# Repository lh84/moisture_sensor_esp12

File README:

# Bodenfeuchte Sensor mit einem ESP12 (Wifi/Wlan)

Dieser Sensor ist noch in Bearbeitung. Es soll dazu dienen, die Bodenfeuchte von Pflanzen zu messen und per WLan an einen Server zur Datenauswertung zu senden. Für das Sender per Wlan wird ein ESP8266 Modul verwendet. Als Sensor kommt eine kapazitive Messmethode zum Einsatz. Das  Grundgerüst des Sensors basiert auf den [Gies-O-Mat von Fred Ram][1].

## Stromquelle

ALs Stromquelle soll ein 18650 AKku dienen, da dieser über hohe Kapazitäten verfügen kann. So kann eine lange Lebensdauer pro Batterie gewährleistet werden. Es wird davon ausgegangen, dass der Sensor bei halbstündiger Messung bis zu 3 Monate arbeiten kann. (Dies muss noch bewiesen werden)

## bisherige Part-Liste

Part       Value          Device     Package  Library        Sheet

1RX-2TX                   PINHD-1X2  1X02     pinhead        1
13,3V-2GND                PINHD-1X2  1X02     pinhead        1
C1         1000µF         CP-SV-E/F  SV-E/F   cap-master     1
C2         10µF           C1206      1206     capsmd         1
C4         10µF           C1206      1206     capsmd         1
ESP                       ESP12      ESP12    esp8266modules 1
GND                       PINHD-1X1  1X01     pinhead        1
IC1        74HC14D        74HC14D    SO14     74xx-eu        1
IC2        HT7333         HT7333     SOT-89   holtek2        1
PAD1                      2,54/1,0   2,54/1,0 wirepad        1
PAD2                      2,54/1,0   2,54/1,0 wirepad        1
PROG       DTSM-6         DTSM-6     DTSM-6   switch-tact    1
R2         ca 100k        R-EU_R0603 R0603    rcl            1
R3         100            R-EU_R0603 R0603    rcl            1
RESET      DTSM-6         DTSM-6     DTSM-6   switch-tact    1
VIN                       PINHD-1X1  1X01     pinhead        1

## Contribute?

Du möchtest mithelfen, dass Design oder die Software zu verbessern? Dann schreib mir oder sende ein Request.

[1]: https://www.mikrocontroller.net/topic/335407

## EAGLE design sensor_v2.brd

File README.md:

REV 1.0

# Moisture Sensor with an ESP8266 12F (Wifi/Wlan)

This project is still work in progress!

This sensor is intended to measure the soil moisture of plants and to send them by WIFI to a server for data evaluation. An ESP8266 module is used for the sender to send data over the air. A capacitive measuring method is used as a sensor to get moisture values. The basic framework of the sensor is based on the [Gies-O-Mat von Fred Ram]<sup>[1]</sup>.

## power source

A 18650 battery is to be used as power source, as this can have high capacities. A long life per battery can be guaranteed. It is assumed that the sensor can operate for up to 3 months at half-hour measurement - This must still be proven!

## Board-Layout

Layout was made with Eagle 7.7<sup>[2]</sup>.

First try to model a case for the board in 3d

GPIO5 is now used to control Vin in smitt trigger to use less power when sensor is not measuring.

## Part-List

| Qty | Value           | Device      | Package     | Parts               | Description                              | Price per pc     | Order-Link                                                                                                                                             | 
|-----|-----------------|-------------|-------------|---------------------|------------------------------------------|------------|--------------------------------------------------------------------------------------------------------------------------------------------------| 
| 2   | PINHD-1X2       | 1X02        | 1RX-2TX     | 3,3V-2GND           | PIN HEADER                               | 0,28 € (0,71 € / 10pc) | https://www.reichelt.de/Buchsenleisten/MPE-115-1-010/3/index.html?ACTION=3&LA=2&ARTICLE=119955&GROUPID=7435&artnr=MPE+115-1-010&SEARCH=%252A     | 
| 1   | 100Ω             |  R-EU_R0603 | R0603       | R3                  | RESISTOR, European symbol                | 0,02 €   | https://www.reichelt.de/SMD-0603-von-0-bis-910-Ohm/RND-0603-1-100/3/index.html?ACTION=3&LA=5&ARTICLE=183013&GROUPID=7967&artnr=RND+0603+1+100    | 
| 1   | 1000µF          | CP-SV-E/F   | SV-E/F      | C1                  |  Big POLARIZED CAP                       | 0,32 €  | https://www.reichelt.de/Elkos-SMD-Low-ESR-105-C/VF-1000-6-3-P-F/3/index.html?ACTION=3&LA=5&ARTICLE=109181&GROUPID=4001&artnr=VF+1000%2F6%2C3+P-F | 
| 2   | 10µF            | C1206       | 1206        | C2, C4              | Small SMD Cap                            | 0,07 €   | https://www.reichelt.de/Vielschicht-SMD-G1206/X7R-G1206-10-16/3/index.html?ACTION=3&LA=5&ARTICLE=89740&GROUPID=8049&artnr=X7R-G1206+10%2F16      | 
| 1   | 500KΩ            | R-TRIMM3374 | R-TRIMM3374 | R1TRIM              | Trimm resistor til 500KΩ                 | 0,67 €  | https://www.reichelt.de/Miniaturtrimmer/23B-500K/3/index.html?ACTION=3&GROUPID=3131&ARTICLE=146090&OFFSET=16&                                    | 
| 1   | 74HC14D 74HC14D | SO14        | IC1         | Hex schmitt trigger | INVERTER                                 | 0,18 €  | https://www.reichelt.de/ICs-74HC-SMD/SMD-HC-14/3/index.html?ACTION=3&GROUPID=2931&ARTICLE=18640&SEARCH=74HC14&OFFSET=16&                         | 
| 2   | DTSM-6  DTSM-6  | DTSM-6      | PROG, RESET |                     | Push button                              | 0,24 €  | https://www.reichelt.de/Kurzhubtaster/TASTER-9314/3/index.html?ACTION=3&GROUPID=7587&ARTICLE=44510&OFFSET=500&                                   | 
| 1   | ESP12           | ESP12       | ESP12       | ESP                 | ESP8266 Wifi module 12                   | 2,54 €  | https://www.aliexpress.com/item/1-pcs-x-ESP-12F-ESP8266-ESP-12F-Remote-Serial-Port-WIFI-Transceiver-Wireless-Module-UNO/32581210212.html         | 
| 1   | HT7333          | HT7333      | SOT-89      | IC2                 | Step Down Module (Ultra low current 4µA) | 0,12 € (1,18€ / 10pc) | https://www.aliexpress.com/item/10PCS-HT7333-A-SOT89-HT7333-1-SOT-89-HT7333A-1-7333-1-SMD-7333A-1-new/32531141419.html                           | 
| 2   | LSP11           | LSP11       | LSP11       | LSP1, LSP2          | SOLDER PAD                               | no costs   |                                                                                                                                                  | 
| 1   | Platine         | EPCU        |             |                     | Size 200X100, one side copper            | 0,58 € (1,75 €) | https://www.reichelt.de/Platinenzuschnitte/EPCU-200X100/3/index.html?ACTION=3&LA=2&ARTICLE=7408&GROUPID=7783&artnr=EPCU+200X100&SEARCH=%252A     |
| 1 | Accu 18650       |         |             |                     | e.g. LG ICR18650S3 - 2200mAh, 3,6 - 3,7V Lithium Ionen Akku | 3,95 € | https://www.akkuteile.de/lg-icr18650s3-2200mah/a-100629 |
| 1 |  18650 Holder     |         |             |                     | | 0,44 € | https://de.aliexpress.com/item/Hot-With-Wire-Lead-Plastic-18650-Battery-3-7V-Clip-Holder-Storage-Box-Case-Cheap-Sale/32458234409.html |
||
|**Sum**||||||**10,00€ + shipping + work**||

Reichelt Order List: https://www.reichelt.de/my/1310317

see also file https://github.com/lh84/moisture_sensor_esp12/blob/master/bom.txt

## Software

As software you can use the source code von Zentris<sup>[3]</sup>. Version 2.2 works pretty good with some small changes.

## Testing

First test at 20/01/17 was pretty good with this new designed board.

## Prototypes

I made a first prototype of the new design with etching at home. Looks und works pretty good for the first test.

## First tests with prototype

You can see the live data from my first sensor prototype monitored in thingspeak:
https://thingspeak.com/channels/210863/charts/1?width=1000&height=600&bgcolor=%23ffffff&color=%23d62020&results=240&type=line&update=15&timescale=240

## Contribute?

You have an idea how this sensor can be designed better? Then write me or send a request.

## TODO
- [ ] Model case for board (fusion 360)
- [ ] Add battery monitoring with voltage devider (http://www.esp8266-projects.com/2015/03/internal-adc-esp8266.html)

## Done
- [x] build first prototype
- [x] check hardware (first prototype)
- [x] check runtime with 18650 battry - see comments in https://github.com/lh84/moisture_sensor_esp12/issues/3
- [x] test hardware in outdoor environment

[1]: https://www.mikrocontroller.net/topic/335407
[2]: https://cadsoft.io/de/
[3]: https://github.com/Zentris/erdfeuchtemessung

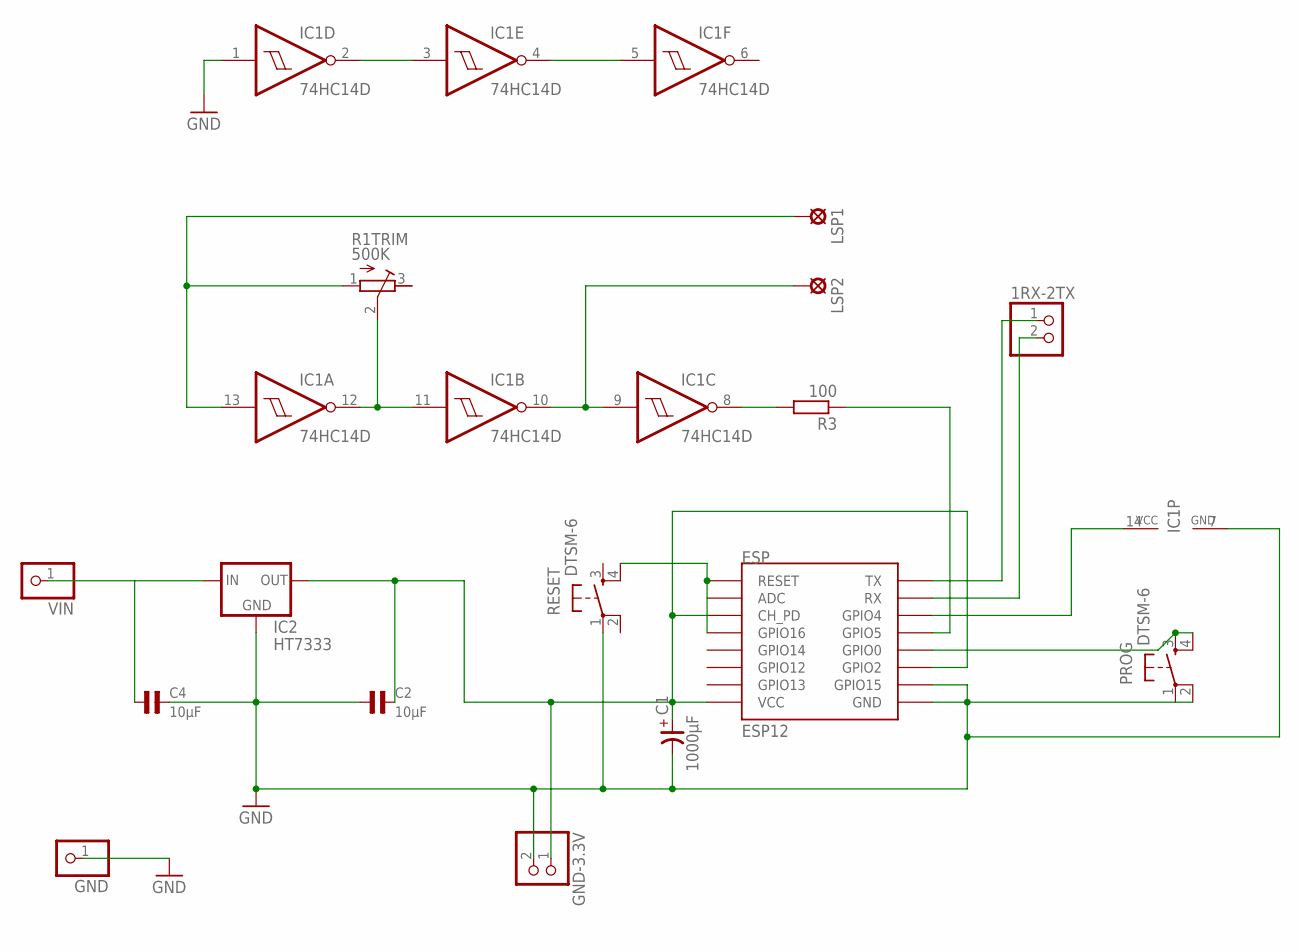
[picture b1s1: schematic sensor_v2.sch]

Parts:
1RX-2TX: PINHD-1X2; 1X02
C1: 1000µF; SV-E/F
C2, C4: 10µF; 1206
ESP: ESP12
GND: PINHD-1X1; 1X01
GND-3.3V: PINHD-1X2; 1X02
IC1: 74HC14D; SO14
IC2: HT7333; SOT-89
LSP1, LSP2: LSP11
PROG: DTSM-6
R1TRIM: 500K; RTRIM3374
R3: 100; R0603
RESET: DTSM-6
VIN: PINHD-1X1; 1X01

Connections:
3.3V: C1.+, C2.2, ESP.CH_PD, ESP.GPIO2, ESP.VCC, GND-3.3V.1, IC2.1 (OUT)
BIS6VVCC: C4.1, IC2.3 (IN), IC2.4 (IN), VIN.1
GND: C1.-, C2.1, C4.2, ESP.GND, ESP.GPIO15, GND.1, GND-3.3V.2, IC1.1 (I), IC1.7 (GND), IC2.2 (GND), PROG.1, PROG.2, RESET.1
unnamed: 1RX-2TX.1, ESP.TX
unnamed: 1RX-2TX.2, ESP.RX
unnamed: ESP.GPIO4, IC1.14 (VCC)
unnamed: ESP.GPIO16, ESP.RESET, RESET.4
unnamed: IC1.2 (O), IC1.3 (I)
unnamed: IC1.4 (O), IC1.5 (I)
unnamed: IC1.9 (I), IC1.10 (O), LSP2.MP
unnamed: IC1.11 (I), IC1.12 (O), R1TRIM.2 (S)
unnamed: ESP.GPIO0, IC1.13 (I), LSP1.MP, PROG.3, PROG.4, R1TRIM.1 (A)
unnamed: IC1.8 (O), R3.2
unnamed: ESP.GPIO5, R3.1

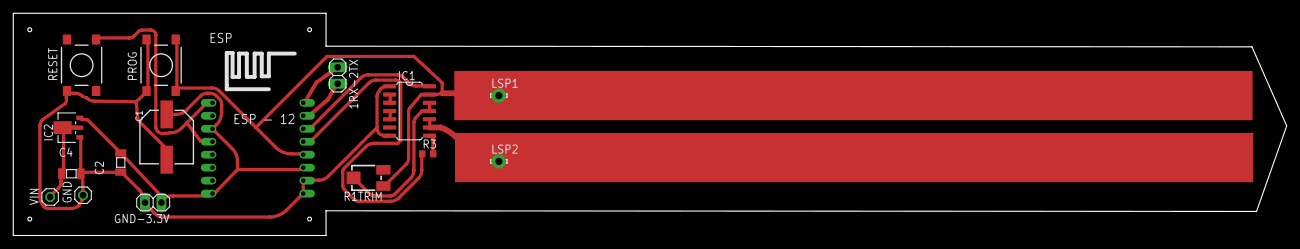
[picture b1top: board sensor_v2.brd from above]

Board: 2 copper layers, 196.5 x 34.3 mm, 16 parts (0 on the bottom side), 14 nets.

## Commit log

2016-08-15 initial commit of moisture sensor
2016-08-16 added mom list wrote readme
2016-08-16 changed Readme
2016-08-26 new read
2016-08-26 deleted unused files
2016-08-26 new readme
2016-08-26 software update
2016-10-30 - updated board to egale 7.7 - first try with ecad.io - first exported 3d model of board
2016-10-30 updated reame
2016-10-30 test superscript
2017-01-22 - new version of board - added trim resistor (500KΩ) to adjust cap. frequency (works like a charm) - better routing - made first real prototype board (self etching) - board works great with Zentris s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
2017-01-22 - added new image of board
2017-02-01 reorder structure for more versions
2017-02-01 new image sensor_in_soil.jpeg
2017-02-02 added excel for bom
2022-02-03 Update LICENSE
